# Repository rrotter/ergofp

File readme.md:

## ergofp
Parses any KiCad s-expression into an object tree for practical manipulation.

## development
Install dependencies: `npm ci`

Run tests: `npm test`

Lint: `npx run lint[:fix]`

Compile sexpr parser: `npm run nearleyc`

Test s-expression parsing pipeline:
- `./demo.js fixtures/sample/footprints.pretty/th_simple_sample.kicad_mod`
- `./demo.js fixtures/sample/sample.kicad_pcb`

### To do:
- add basic manipulation to Footprint
  - rotation
  - translation
  - stamping w/ PCB data
- generate demo kicad_pcb
  - headers
  - insert footprints
  - add nets
- generate kicad_pcb using ergogen points data
- Test loading files in a web browser, via client side js
  - `subtree` common footprints
  - experiment with `access-control-allow-origin` (CORS) on GitHub pages for external hosting of alternative footprints

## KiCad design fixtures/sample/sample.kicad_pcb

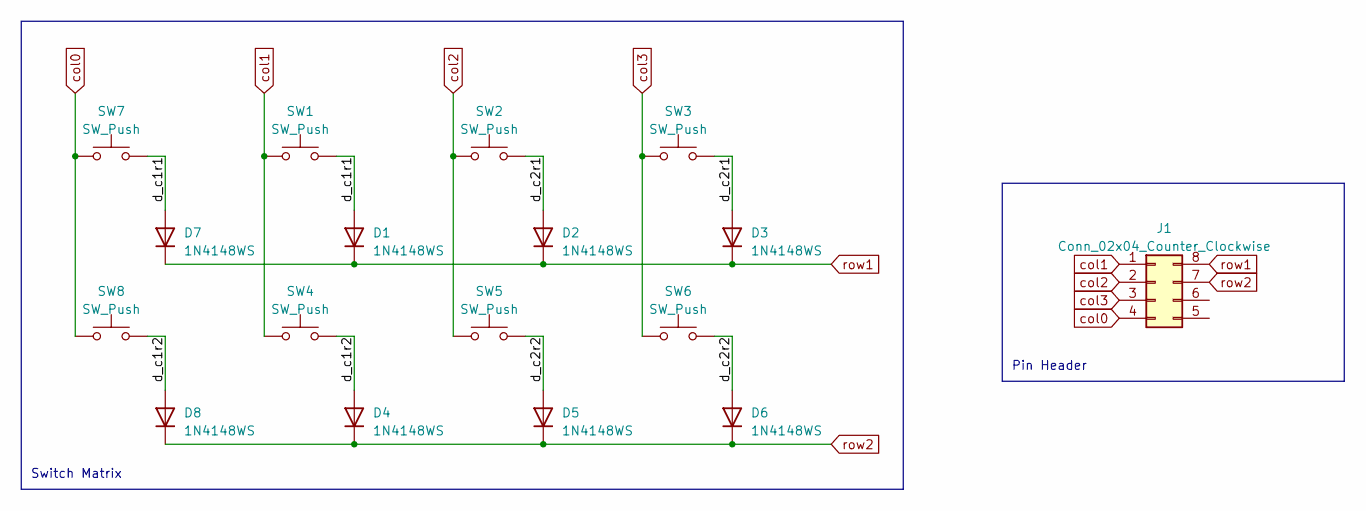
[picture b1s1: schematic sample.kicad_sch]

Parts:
D1, D2, D3, D4, D5, D6, D7, D8: 1N4148WS; D_SOD-323_HandSoldering
J1: Conn_02x04_Counter_Clockwise; PinHeader_2x04_P2.54mm_Vertical
SW1, SW2, SW3, SW7: SW_Push; smd_simple_sample
SW4, SW5, SW6, SW8: SW_Push; th_simple_sample

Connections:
/d_c1r1: D1.2 (A), D7.2 (A), SW1.2, SW7.2
/d_c1r2: D4.2 (A), D8.2 (A), SW4.2, SW8.2
/d_c2r1: D2.2 (A), D3.2 (A), SW2.2, SW3.2
/d_c2r2: D5.2 (A), D6.2 (A), SW5.2, SW6.2
col0: J1.4, SW7.1, SW8.1
col1: J1.1, SW1.1, SW4.1
col2: J1.2, SW2.1, SW5.1
col3: J1.3, SW3.1, SW6.1
row1: D1.1 (K), D2.1 (K), D3.1 (K), D7.1 (K), J1.8
row2: D4.1 (K), D5.1 (K), D6.1 (K), D8.1 (K), J1.7

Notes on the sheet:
Pin Header
Switch Matrix

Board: 2 copper layers, 17 parts (8 on the bottom side), 10 nets, no tracks yet.

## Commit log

2023-06-04 initial commit
    - stub out tests
    - js boilerplate
    - sample KiCad project for reference
2023-08-08 Wrapper objects for fetching footprints
2023-08-09 add sexp parser
2023-08-10 fix handling of \ in qwords
2023-08-12 add parser demo code, improve qword handling
2023-08-13 rename sexpr.* -> grammar.*
2023-08-13 Add parsing to Footprint class
    - add SExpression class (parent of Footprint)
    - Footprint.toString now is reconstructed from parsed data
2023-08-13 refactor test code
2023-08-13 .name(), .type() accessors
2023-08-13 SExpression factory methods
    - .fromString should replace all previous usage of child class constructors
    - .fromTree to allow creation of SExpression objects from subtrees
2023-08-14 use Standard JS linter
2023-08-14 readme spelling
2023-08-14 require node 20, because 18 doesn't work
2023-08-28 Bump chai from 4.3.7 to 4.3.8
    Bumps [chai](https://github.com/chaijs/chai) from 4.3.7 to 4.3.8.
    - [Release notes](https://github.com/chaijs/chai/releases)
    - [Changelog](https://github.com/chaijs/chai/blob/4.x.x/History.md)
    - [Commits](https://github.com/chaijs/chai/compare/v4.3.7...v4.3.8)
    ---
    updated-dependencies:
2023-09-11 Bump actions/checkout from 3 to 4
    Bumps [actions/checkout](https://github.com/actions/checkout) from 3 to 4.
    - [Release notes](https://github.com/actions/checkout/releases)
    - [Changelog](https://github.com/actions/checkout/blob/main/CHANGELOG.md)
    - [Commits](https://github.com/actions/checkout/compare/v3...v4)
    ---
    updated-dependencies:
2023-09-27 Bump get-func-name from 2.0.0 to 2.0.2
    Bumps [get-func-name](https://github.com/chaijs/get-func-name) from 2.0.0 to 2.0.2.
    - [Release notes](https://github.com/chaijs/get-func-name/releases)
    - [Commits](https://github.com/chaijs/get-func-name/commits/v2.0.2)
    ---
    updated-dependencies:
    - dependency-name: get-func-name
2023-10-02 Bump chai from 4.3.7 to 4.3.10
    Bumps [chai](https://github.com/chaijs/chai) from 4.3.7 to 4.3.10.
    - [Release notes](https://github.com/chaijs/chai/releases)
    - [Changelog](https://github.com/chaijs/chai/blob/4.x.x/History.md)
    - [Commits](https://github.com/chaijs/chai/compare/v4.3.7...v4.3.10)
    ---
    updated-dependencies:
2023-10-30 Bump actions/setup-node from 3 to 4
    Bumps [actions/setup-node](https://github.com/actions/setup-node) from 3 to 4.
    - [Release notes](https://github.com/actions/setup-node/releases)
    - [Commits](https://github.com/actions/setup-node/compare/v3...v4)
    ---
    updated-dependencies:
    - dependency-name: actions/setup-node
